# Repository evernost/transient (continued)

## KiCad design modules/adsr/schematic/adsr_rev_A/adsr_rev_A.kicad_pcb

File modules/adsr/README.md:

# ADSR - Contour Generator

Contour Generator: Attack, Decay, Sustain, Release.

---

## Overview

- **Type:** Envelope Generator
- **Domain:** Analog
- **Status:** Work in progress

Block diagram: TODO!

---

## Features
- End of ADSR status (required for the voice assignment in polyphony)

---

## Interfaces

### Inputs
| Name | Type | Range | Description |
|-----|------|-------|-------------|
| IN | Audio | ±1V | Input signal |
| AMP_CV | Analog | 0–5 V | Volume control |

### Outputs
| Name | Type | Description |
|------|------|-------------|
| OUT | Audio | Filtered signal |

---

## Controls

| Control | Type | Description |
|--------|------|-------------|
| Cutoff | Potentiometer | Manual cutoff frequency |
| Resonance | Potentiometer | Feedback amount |

---

## Electrical Characteristics

- **Supply voltage:** +/-12V
- **Current consumption:** TBD mA
- **Signal levels:** TBD

---

## Implementation Notes
Section is TODO.

---

## Files

| File                          | Description                           |
|-------------------------------|---------------------------------------|
| `adsr_rev_A.pdf`              | Electrical schematic (PDF export)     |
| `adsr_rev_A.kicad_sch`        | Schematic (KiCad 10.0.8)              |
| `adsr_rev_A.kicad_pcb`        | PCB layout (KiCad 10.0.8)             |
| `sim/adsr_output_stage.asc`   | SPICE simulation of the output buffer |

---

## Tools
Designed with KiCAD 10.0.8

### KiCAD Grid Settings

| Name   | Size    | Description        |
|--------|---------|--------------------|
| Grid 1 | 0.25 mm | PCB outline        |
| Grid 2 | 25 mil  | Parts placement    |
| Grid 3 | 25 mil  | Routing            |

**Rationale**: Grid 2 and Grid 3 were initially 50 mil, but turned out to be too coarse for precise tracks.

### KiCAD Track settings

| Name    | Size   | Description                |
|---------|--------|----------------------------|
| Class 1 | 500 um | Regular tracks (signal)    |
| Class 2 | 800 um | Power tracks               |

---

## Calibration / Tuning
- Tune the bias voltage on $Q_5$ and $Q_{11}$
- Tune the quiescent current 
- Tune the overload threshold

---

## Known Issues / TODO

- [ ] Make the bias point higher: 1.6V might clip too early
- [ ] Add a reverse polarity protection

---

## Revision History

| Revision  | Date          | Notes             |
|-----------|---------------|-------------------|
| Rev A     | YYYY-MM-DD    | First prototype   |
| Rev B     | YYYY-MM-DD    |                   |

---

## Related Modules

Links to other submodules in the repository:
- `../vca/`
- `../ring_modulator/`

---

## References
- ARP Odyssey Schematic

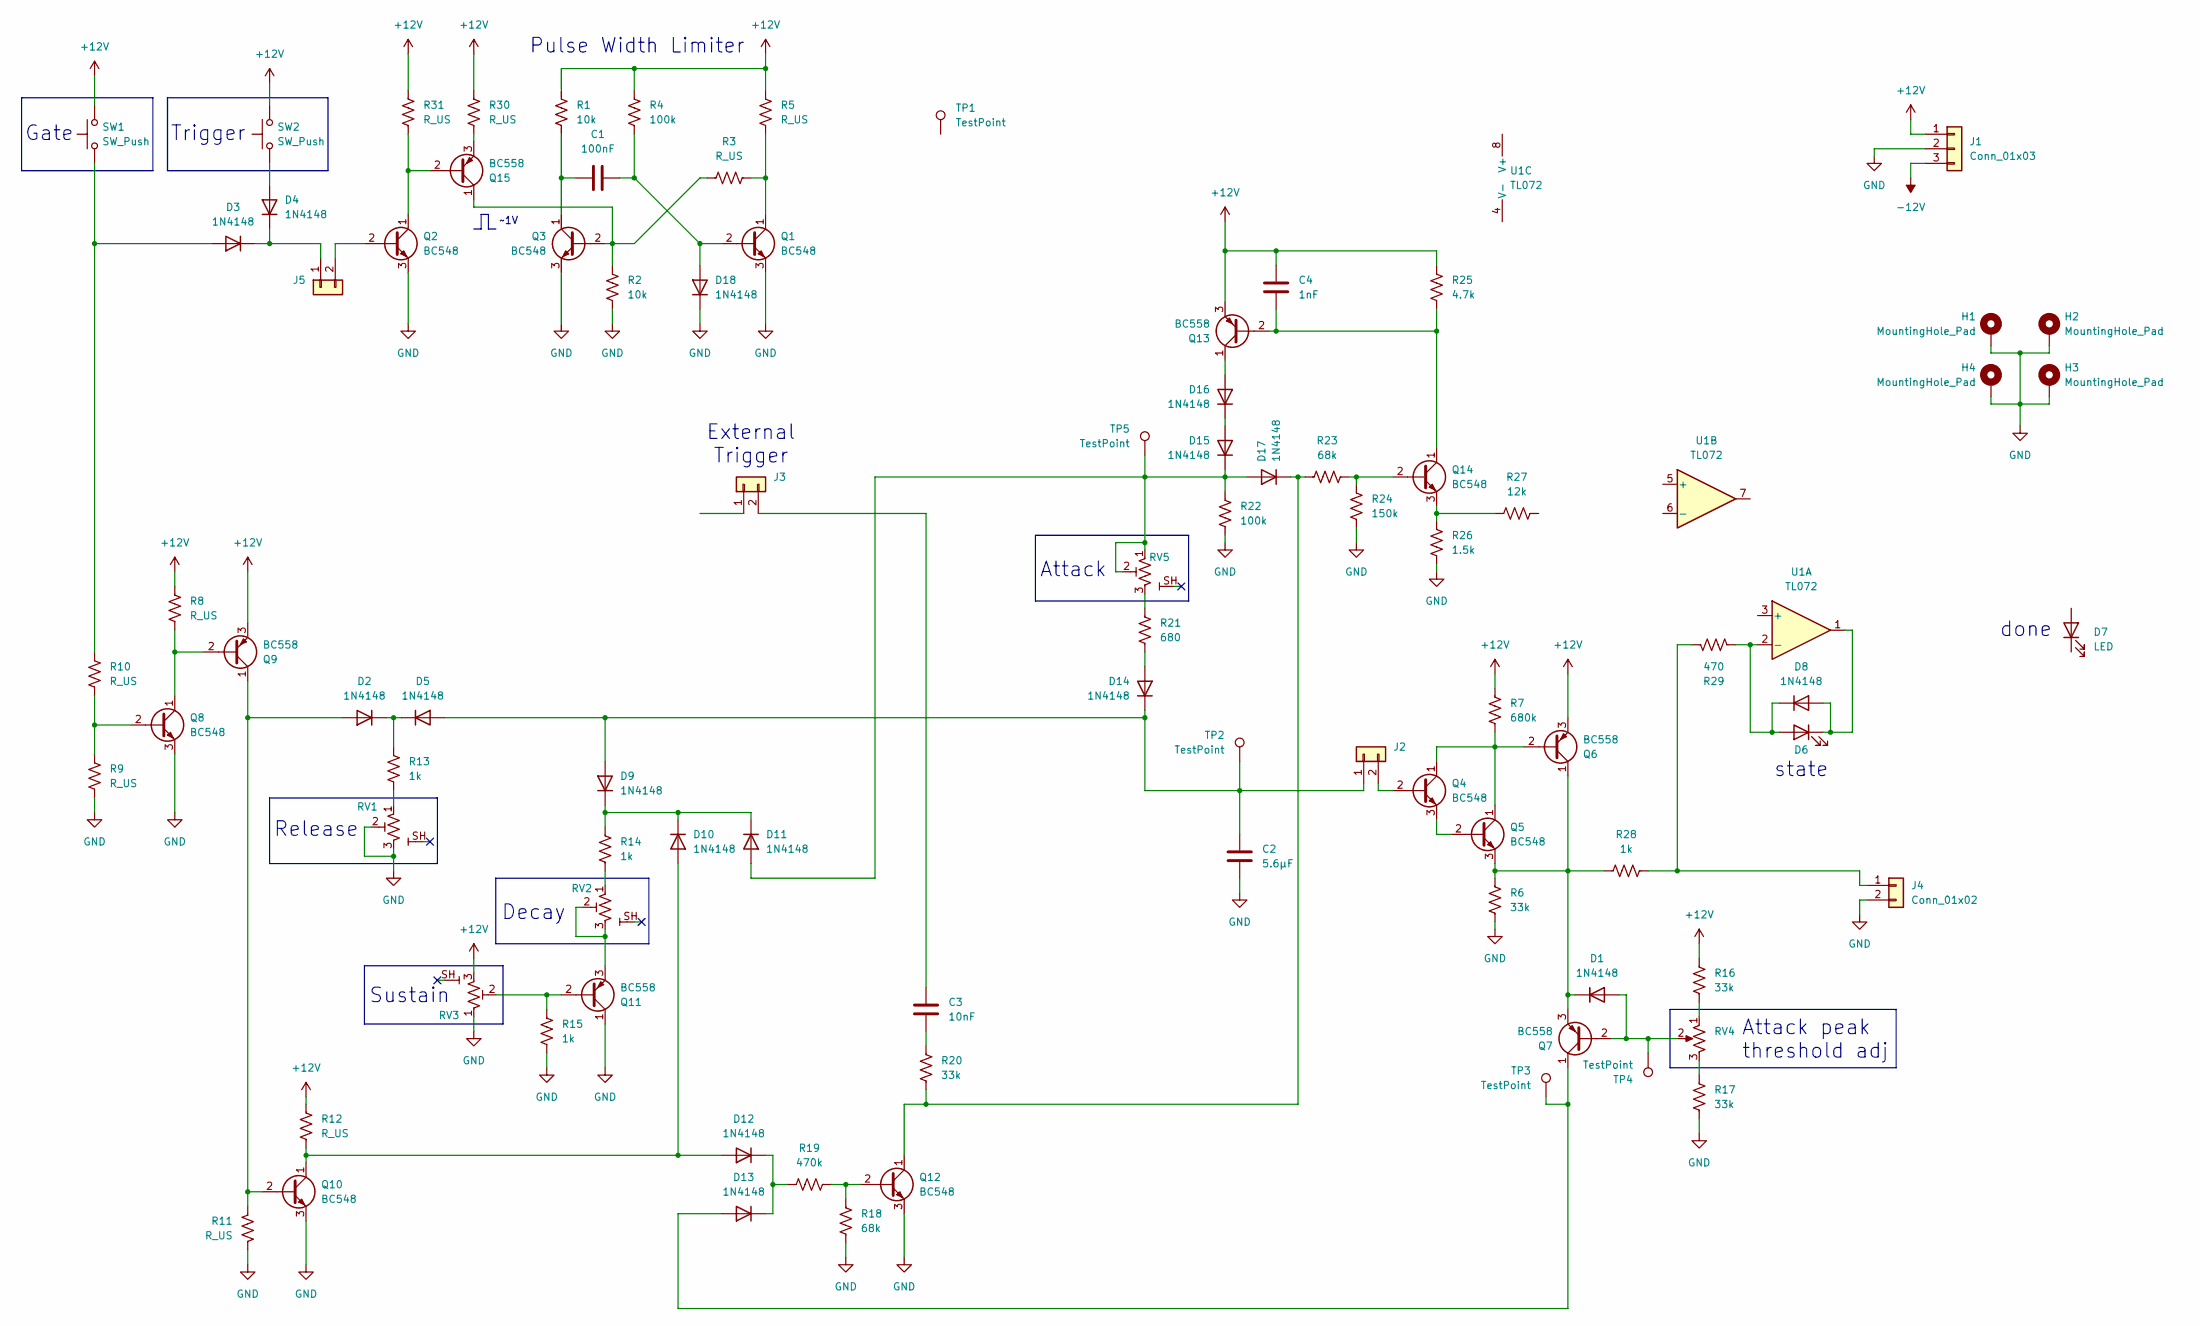
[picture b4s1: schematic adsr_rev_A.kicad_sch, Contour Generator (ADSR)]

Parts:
C1: 100nF; C_Rect_L7.0mm_W2.0mm_P5.00mm
C2: 5.6µF; C_Rect_L13.0mm_W6.0mm_P10.00mm_FKS3_FKP3_MKS4
C3: 10nF; C_Rect_L13.0mm_W6.0mm_P10.00mm_FKS3_FKP3_MKS4
C4: 1nF; C_Rect_L13.0mm_W6.0mm_P10.00mm_FKS3_FKP3_MKS4
D1, D2, D3, D4, D5, D8, D9, D10, D11, D12, D13, D14, D15, D16, D17, D18: 1N4148; D_DO-35_SOD27_P10.16mm_Horizontal
D6, D7: LED; LED_D3.0mm
H1, H2, H3, H4: MountingHole_Pad; MountingHole_3.2mm_M3_Pad_Via
J1: Conn_01x03; WuerthElectronik_WR_TBL_Series_2545_1x03_P5.08mm_Horizontal
J2, J3, J4, J5: Conn_01x02; PinHeader_1x02_P2.54mm_Vertical
Q1, Q2, Q3, Q4, Q5, Q8, Q10, Q12, Q14: BC548; TO-92L_Inline_Wide
Q6, Q7, Q9, Q11, Q13, Q15: BC558; TO-92L_Inline_Wide
R1, R2: 10k; R_Axial_DIN0207_L6.3mm_D2.5mm_P10.16mm_Horizontal
R3, R5, R8, R9, R10, R11, R12, R30, R31: R_US; R_Axial_DIN0207_L6.3mm_D2.5mm_P10.16mm_Horizontal
R4, R22: 100k; R_Axial_DIN0207_L6.3mm_D2.5mm_P10.16mm_Horizontal
R6, R16, R17, R20: 33k; R_Axial_DIN0207_L6.3mm_D2.5mm_P10.16mm_Horizontal
R7: 680k; R_Axial_DIN0207_L6.3mm_D2.5mm_P10.16mm_Horizontal
R13, R14, R15, R28: 1k; R_Axial_DIN0207_L6.3mm_D2.5mm_P10.16mm_Horizontal
R18, R23: 68k; R_Axial_DIN0207_L6.3mm_D2.5mm_P10.16mm_Horizontal
R19: 470k; R_Axial_DIN0207_L6.3mm_D2.5mm_P10.16mm_Horizontal
R21: 680; R_Axial_DIN0207_L6.3mm_D2.5mm_P10.16mm_Horizontal
R24: 150k; R_Axial_DIN0207_L6.3mm_D2.5mm_P10.16mm_Horizontal
R25: 4.7k; R_Axial_DIN0207_L6.3mm_D2.5mm_P10.16mm_Horizontal
R26: 1.5k; R_Axial_DIN0207_L6.3mm_D2.5mm_P10.16mm_Horizontal
R27: 12k; R_Axial_DIN0207_L6.3mm_D2.5mm_P10.16mm_Horizontal
R29: 470; R_Axial_DIN0207_L6.3mm_D2.5mm_P10.16mm_Horizontal
RV1, RV2, RV3, RV5: R_Potentiometer_Shield_US; Potentiometer_Bourns_PTV09A-4_Single_Vertical
RV4: R_Potentiometer_US; Potentiometer_Bourns_3296W_Vertical
SW1, SW2: SW_Push; SW_Push_1P1T_NO_CK_KSC6xxG
TP1, TP2, TP3, TP4, TP5: TestPoint; TestPoint_Pad_D2.0mm
U1: TL072; DIP-8_W7.62mm_LongPads

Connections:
+12V: C4.1, J1.1, Q6.3 (E), Q9.3 (E), Q13.3 (E), R1.1, R4.1, R5.1, R7.1, R8.1, R12.1, R16.1, R25.2, R30.1, R31.1, RV3.3 (B), SW1.2, SW2.2
-12V: J1.3
GND: C2.2, D18.1 (K), H1.1 (1_1), H2.1 (1_1), H3.1 (1_1), H4.1 (1_1), J1.2, J4.2, Q1.3 (E), Q2.3 (E), Q3.3 (E), Q8.3 (E), Q10.3 (E), Q11.1 (C), Q12.3 (E), R2.2, R6.2, R9.2, R11.2, R15.2, R17.2, R18.2, R22.2, R24.1, R26.1, RV1.2 (W), RV1.3 (B), RV3.1 (A)
unnamed: C3.2, R20.1
unnamed: D1.2 (A), Q7.2 (B), RV4.2, TP4.1 (1_1)
unnamed: D1.1 (K), Q5.3 (E), Q6.1 (C), Q7.3 (E), R6.1, R28.2
unnamed: D2.2 (A), Q9.1 (C), Q10.2 (B), R11.1
unnamed: D2.1 (K), D5.1 (K), R13.1
unnamed: D3.2 (A), R10.1, SW1.1
unnamed: D3.1 (K), D4.1 (K), J5.1
unnamed: D4.2 (A), SW2.1
unnamed: D6.2 (A), D8.1 (K), R29.1, U1.2 (-_2)
unnamed: D6.1 (K), D8.2 (A), U1.1
unnamed: D10.2 (A), D12.2 (A), Q10.1 (C), R12.2
unnamed: D9.1 (K), D10.1 (K), D11.1 (K), R14.1
unnamed: D11.2 (A), D15.1 (K), D17.2 (A), R22.1, RV5.1 (A), RV5.2 (W), TP5.1 (1_1)
unnamed: D12.1 (K), D13.1 (K), R19.1
unnamed: D13.2 (A), Q7.1 (C), TP3.1 (1_1)
unnamed: D14.2 (A), R21.2
unnamed: C2.1, D5.2 (A), D9.2 (A), D14.1 (K), J2.1, TP2.1 (1_1)
unnamed: D15.2 (A), D16.1 (K)
unnamed: D16.2 (A), Q13.1 (C)
unnamed: D17.1 (K), Q12.1 (C), R20.2, R23.1
unnamed: C1.2, D18.2 (A), Q1.2 (B), R4.2
unnamed: J2.2, Q4.2 (B)
unnamed: C3.1, J3.2 (Pin_2_2)
unnamed: J4.1, R28.1, R29.2
unnamed: J5.2, Q2.2 (B)
unnamed: Q1.1 (C), R3.2, R5.2
unnamed: C1.1, Q3.1 (C), R1.2
unnamed: Q4.1 (C), Q5.1 (C), Q6.2 (B), R7.2
unnamed: Q4.3 (E), Q5.2 (B)
unnamed: Q8.2 (B), R9.1, R10.2
unnamed: Q8.1 (C), Q9.2 (B), R8.2
unnamed: Q11.2 (B), R15.1, RV3.2 (W)
unnamed: Q11.3 (E), RV2.2 (W), RV2.3 (B)
unnamed: Q12.2 (B), R18.1, R19.2
unnamed: C4.2, Q13.2 (B), Q14.1 (C), R25.1
unnamed: Q14.2 (B), R23.2, R24.2
unnamed: Q14.3 (E), R26.2, R27.2
unnamed: Q2.1 (C), Q15.2 (B), R31.2
unnamed: Q3.2 (B), Q15.1 (C), R2.1, R3.1
unnamed: Q15.3 (E), R30.2
unnamed: R16.2, RV4.1
unnamed: R17.1, RV4.3
unnamed: R13.2, RV1.1 (A)
unnamed: R14.2, RV2.1 (A)
unnamed: R21.1, RV5.3 (B)

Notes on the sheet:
Decay
Attack peak threshold adj
Trigger
Gate
Pulse Width Limiter
External Trigger
Attack
Release
~1V
Sustain
state
done

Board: 2 copper layers, 90 parts (0 on the bottom side), 47 nets, no tracks yet.

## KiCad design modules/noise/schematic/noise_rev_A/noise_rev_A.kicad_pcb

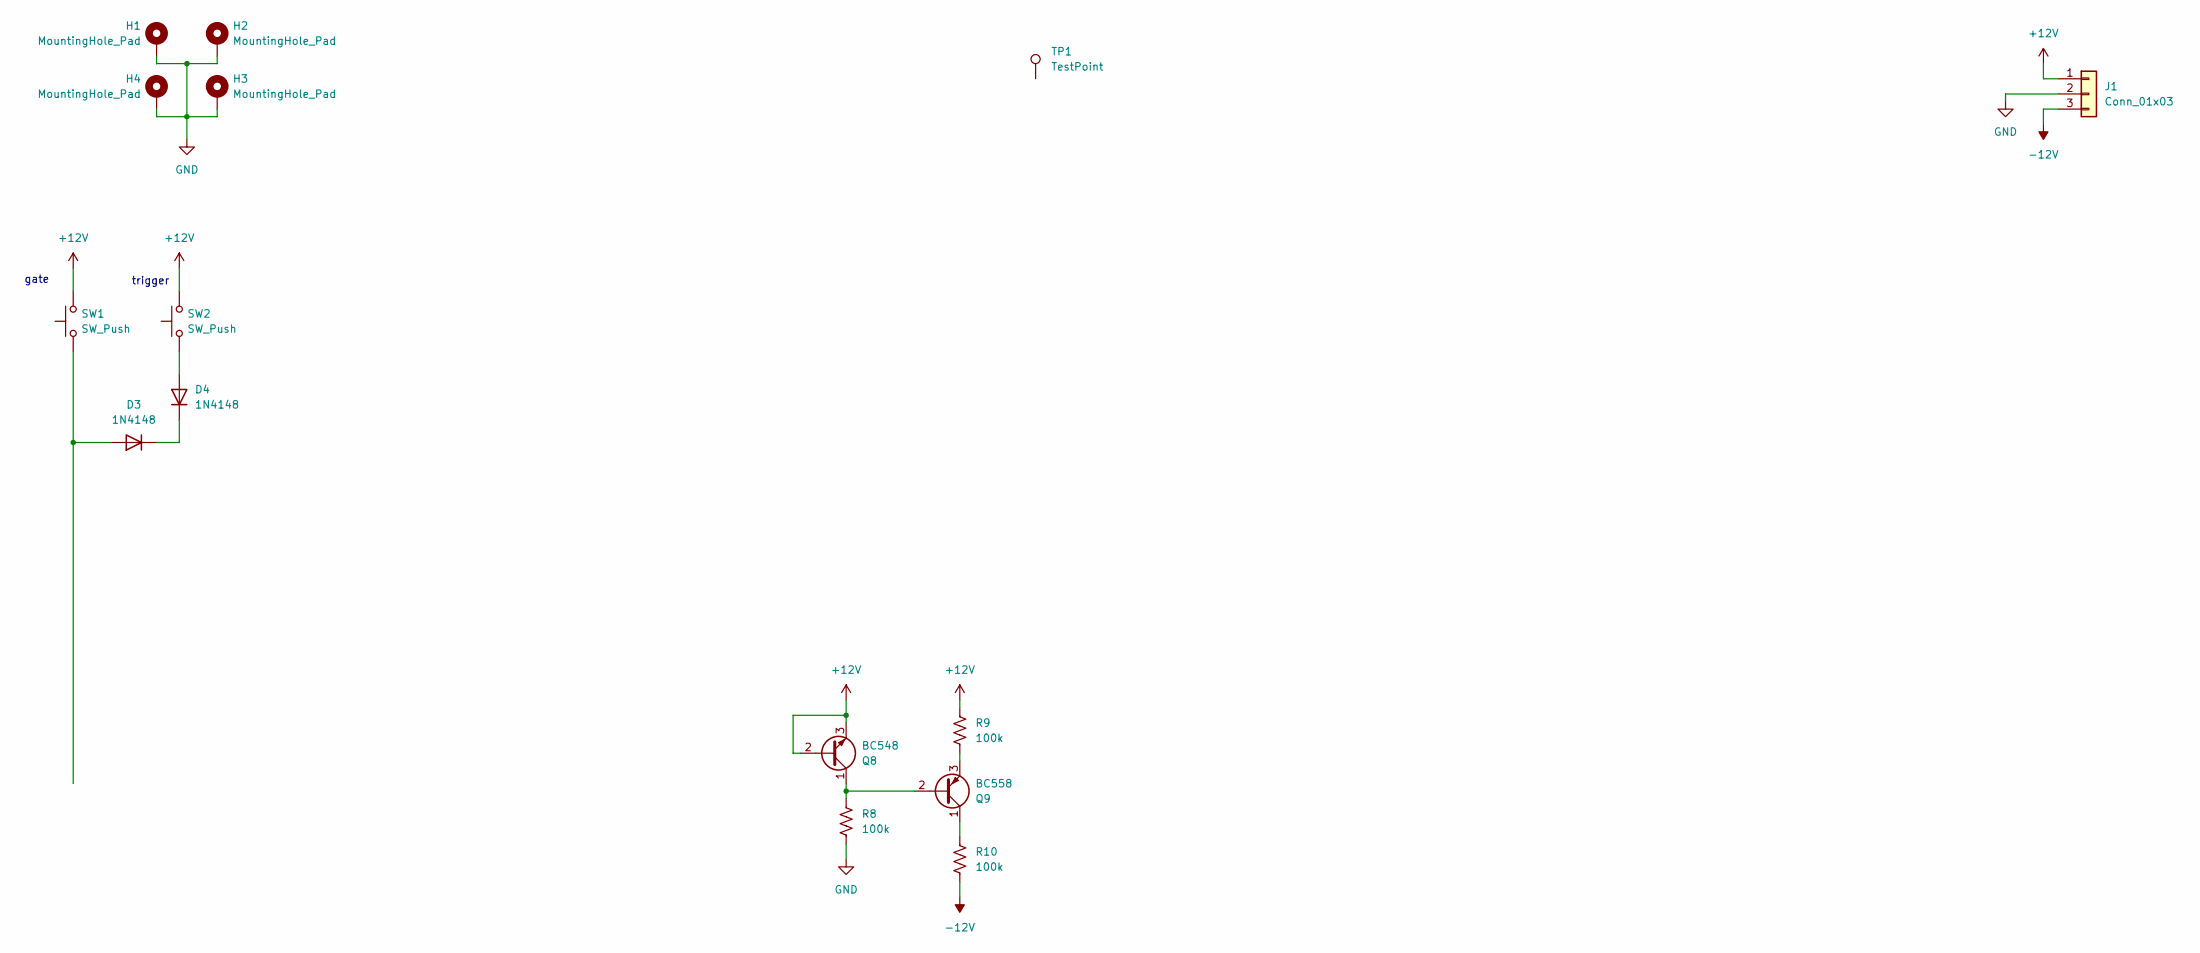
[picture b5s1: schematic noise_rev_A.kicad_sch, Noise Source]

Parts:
D3, D4: 1N4148; D_DO-35_SOD27_P10.16mm_Horizontal
H1, H2, H3, H4: MountingHole_Pad; MountingHole_3.2mm_M3_Pad_Via
J1: Conn_01x03; WuerthElectronik_WR_TBL_Series_2545_1x03_P5.08mm_Horizontal
Q8: BC548; TO-92L_Inline_Wide
Q9: BC558; TO-92L_Inline_Wide
R8, R9, R10: 100k; R_Axial_DIN0207_L6.3mm_D2.5mm_P10.16mm_Horizontal
SW1, SW2: SW_Push; SW_Push_1P1T_NO_CK_KSC6xxG
TP1: TestPoint; TestPoint_Pad_D2.0mm

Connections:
+12V: J1.1, Q8.2 (B), Q8.3 (E), R9.1, SW1.2, SW2.2
-12V: J1.3, R10.2
GND: H1.1 (1_1), H2.1 (1_1), H3.1 (1_1), H4.1 (1_1), J1.2, R8.2
unnamed: D3.2 (A), SW1.1
unnamed: D3.1 (K), D4.1 (K)
unnamed: D4.2 (A), SW2.1
unnamed: Q8.1 (C), Q9.2 (B), R8.1
unnamed: Q9.1 (C), R10.1
unnamed: Q9.3 (E), R9.2

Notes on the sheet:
trigger
gate

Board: 2 copper layers, 15 parts (0 on the bottom side), 9 nets, no tracks yet.

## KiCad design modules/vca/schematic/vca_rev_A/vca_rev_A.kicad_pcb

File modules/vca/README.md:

# VCA Module

A simple analog Voltage-Controlled Amplifier for audio signals.

---

## Overview

- **Type:** VCA
- **Domain:** Analog
- **Status:** Work in progress

Block diagram: TODO!

---

## Features
- **Overdrive**: the input can be overdriven on purpose to add _colors_ to the function
- **Control**: linear and logarithmic control

---

## Interfaces

### Inputs
| Name | Type | Range | Description |
|-----|------|-------|-------------|
| IN | Audio | ±1V | Input signal |
| AMP_CV | Analog | 0–5 V | Volume control |

### Outputs
| Name | Type | Description |
|------|------|-------------|
| OUT | Audio | Filtered signal |

---

## Controls

| Control | Type | Description |
|--------|------|-------------|
| Cutoff | Potentiometer | Manual cutoff frequency |

---

## Electrical Characteristics

- **Supply voltage:** ±12V
- **Current consumption:** TBD mA
- **Signal levels:** TBD

---

## Implementation Notes
Section is TODO.

---

## Files

| File                  | Description                       |
|-----------------------|-----------------------------------|
| `vca_rev_A.pdf`       | Electrical schematic (PDF export) |
| `vca_rev_A.kicad_sch` | Schematic (KiCad 10.0.8)          |
| `vca_rev_A.kicad_pcb` | PCB layout (KiCad 10.0.8)         |
| `sim/XXX.asc`         | SPICE simulation                  |

---

## Tools
Designed with KiCAD 10.0.8

### KiCAD Grid Settings

| Name   | Size    | Description        |
|--------|---------|--------------------|
| Grid 1 | 0.25 mm | PCB outline        |
| Grid 2 | 25 mil  | Parts placement    |
| Grid 3 | 25 mil  | Routing            |

**Rationale**: Grid 2 and Grid 3 were initially 50 mil, but turned out to be too coarse for precise tracks.

### KiCAD Track settings

| Name    | Size   | Description                |
|---------|--------|----------------------------|
| Class 1 | 500 um | Regular traces (signal)    |
| Class 2 | 800 um | Power traces               |

---

## Calibration / Tuning
No calibration required.

---

## Known Issues / TODO

- [ ] TODO

---

## Revision History

| Revision | Date | Notes |
|--------|------|-------|
| Rev A | YYYY-MM-DD | Initial prototype |

---

## Related Modules

Links to other submodules in the repository:
- `../vca/`
- `../ring_modulator/`

---

## References

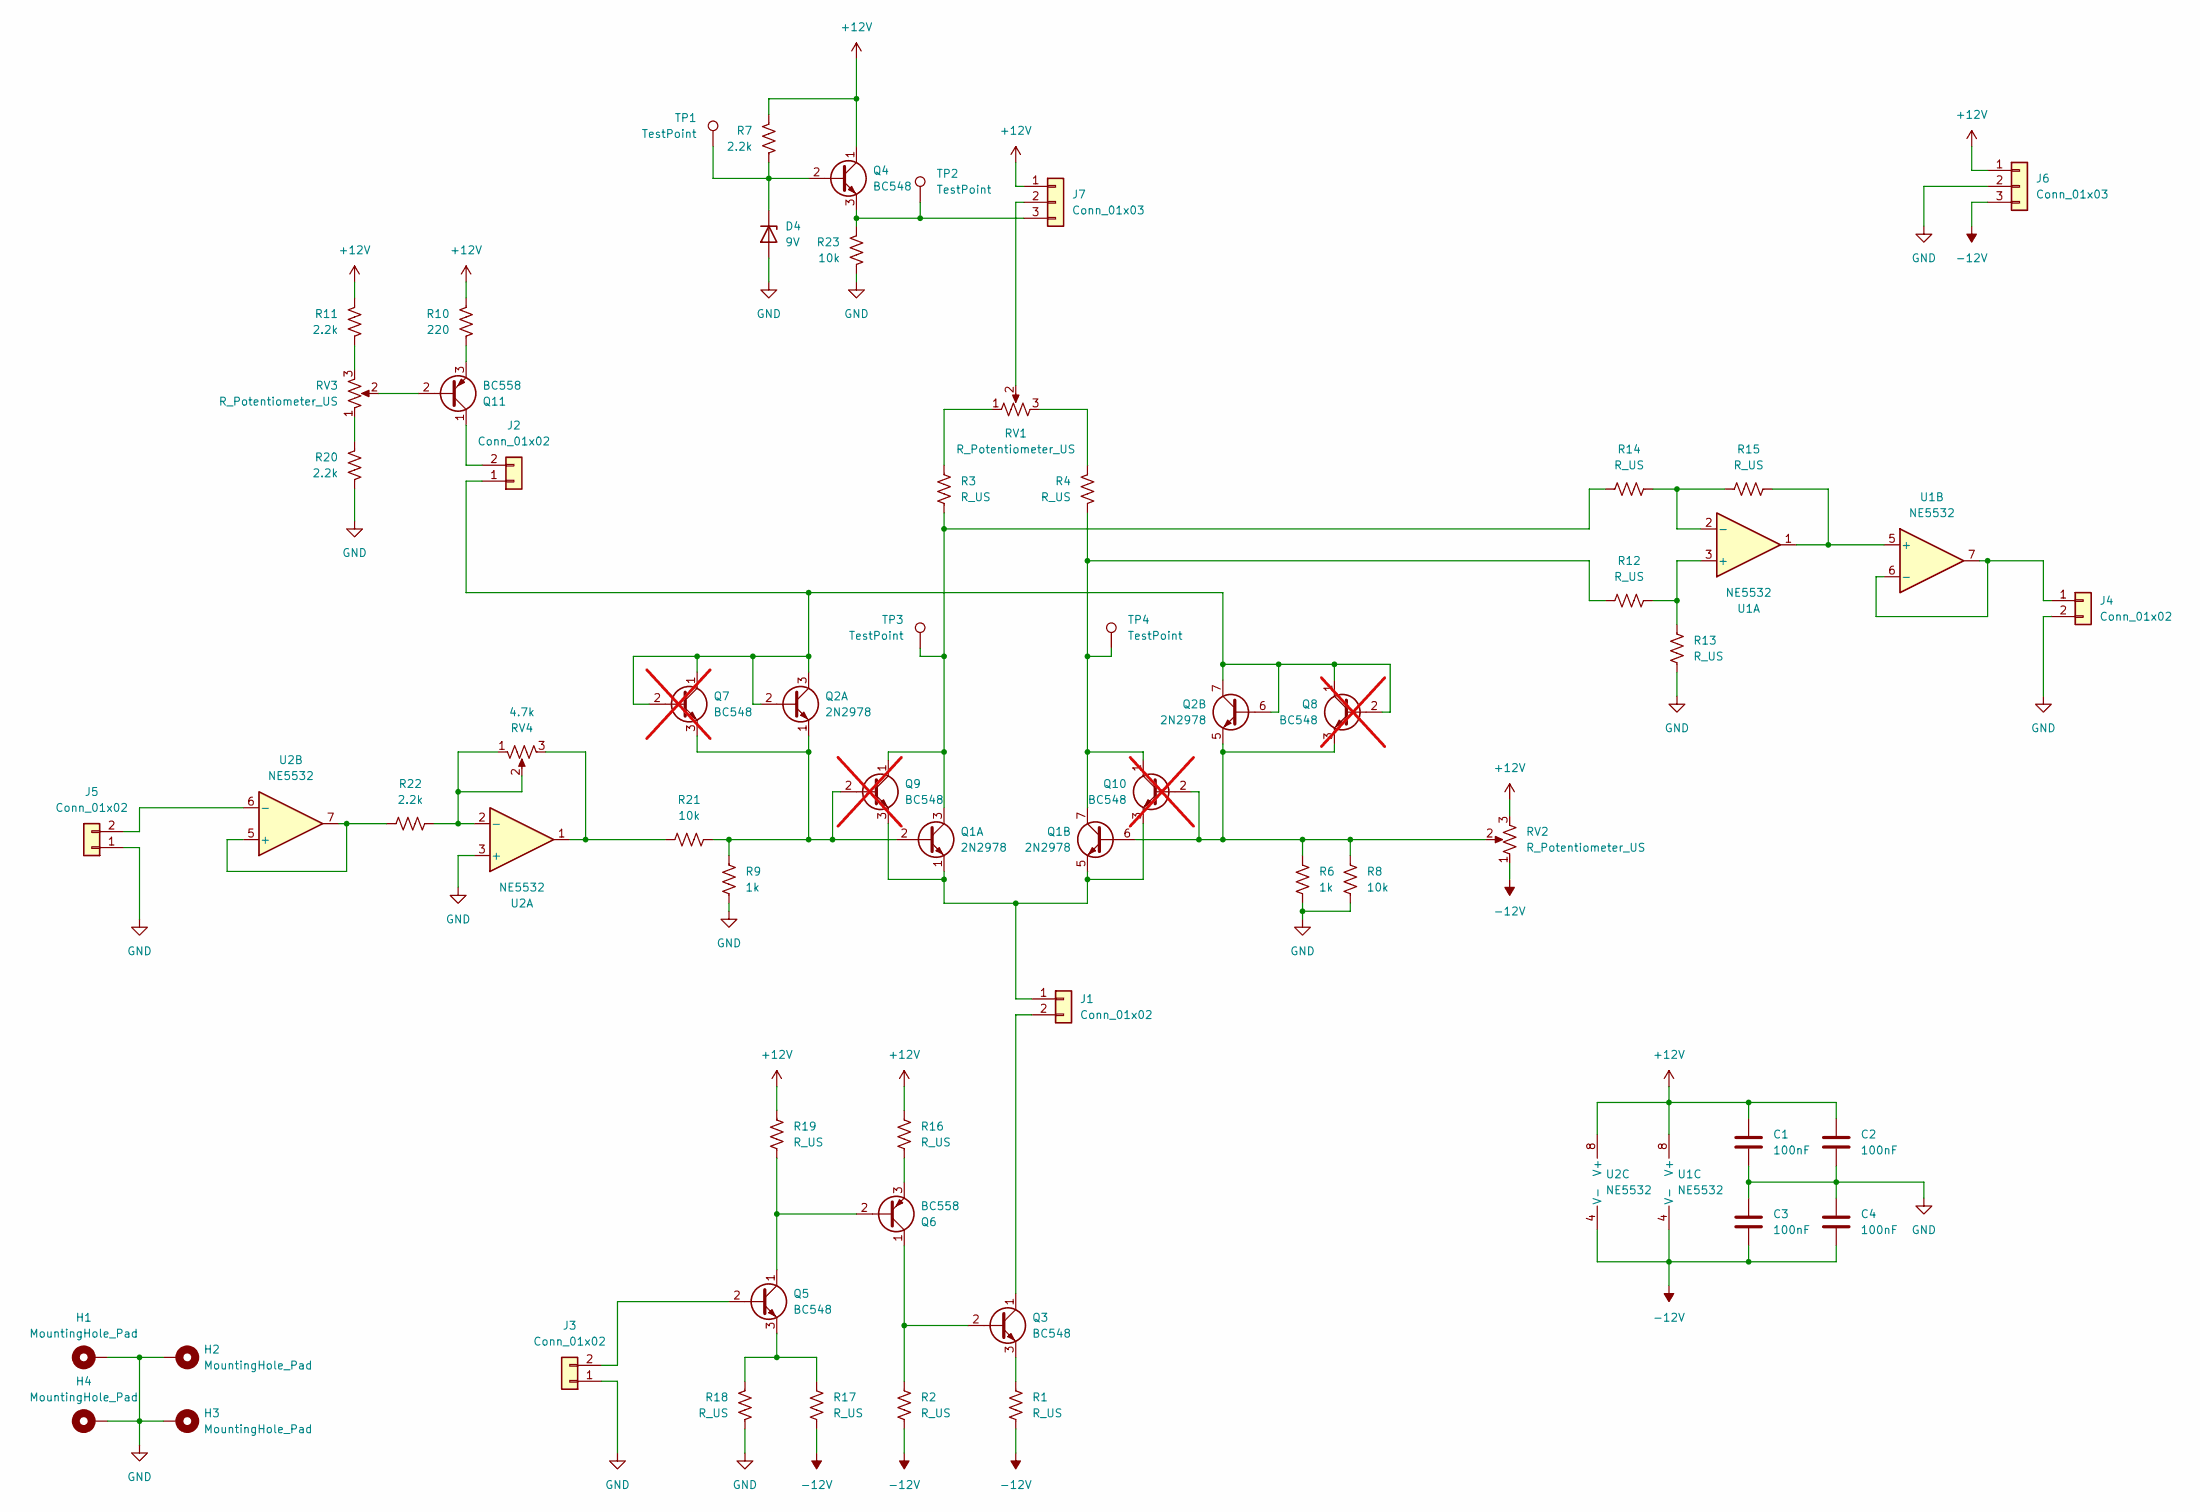
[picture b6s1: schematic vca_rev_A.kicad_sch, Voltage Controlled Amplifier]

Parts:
C1, C2, C3, C4: 100nF; C_Rect_L7.0mm_W2.0mm_P5.00mm
D4: 9V; D_DO-41_SOD81_P10.16mm_Horizontal
H1, H2, H3, H4: MountingHole_Pad; MountingHole_3.2mm_M3_Pad_Via
J1, J2, J3, J4, J5: Conn_01x02; PinHeader_1x02_P2.54mm_Vertical
J6: Conn_01x03; WuerthElectronik_WR_TBL_Series_2545_1x03_P5.08mm_Horizontal
J7: Conn_01x03; PinSocket_1x03_P2.54mm_Vertical
Q1, Q2: 2N2978; TO-5-6
Q3, Q4, Q5: BC548; TO-92L_Inline_Wide
Q6, Q11: BC558; TO-92L_Inline_Wide
Q7, Q8, Q9, Q10: BC548; TO-92L_Inline_Wide; not fitted
R1, R2, R3, R4, R12, R13, R14, R15, R16, R17, R18, R19: R_US; R_Axial_DIN0207_L6.3mm_D2.5mm_P10.16mm_Horizontal
R6, R9: 1k; R_Axial_DIN0207_L6.3mm_D2.5mm_P10.16mm_Horizontal
R7, R11, R20, R22: 2.2k; R_Axial_DIN0207_L6.3mm_D2.5mm_P10.16mm_Horizontal
R8, R21, R23: 10k; R_Axial_DIN0207_L6.3mm_D2.5mm_P10.16mm_Horizontal
R10: 220; R_Axial_DIN0207_L6.3mm_D2.5mm_P10.16mm_Horizontal
RV1, RV2, RV3: R_Potentiometer_US; Potentiometer_Bourns_3296W_Vertical
RV4: 4.7k; Potentiometer_Bourns_3296W_Vertical
TP1, TP2, TP3, TP4: TestPoint; TestPoint_Pad_D2.0mm
U1, U2: NE5532; SOIC-8_5.3x6.2mm_P1.27mm

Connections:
+12V: C1.1, C2.1, J6.1, J7.1, Q4.1 (C), R7.1, R10.1, R11.1, R16.1, R19.1, RV2.3, U1.8 (V+), U2.8 (V+)
-12V: C3.2, C4.2, J6.3, R1.2, R2.2, R17.2, RV2.1, U1.4 (V-), U2.4 (V-)
GND: C1.2, C2.2, C3.1, C4.1, D4.2 (A), H1.1 (1_1), H2.1 (1_1), H3.1 (1_1), H4.1 (1_1), J3.1, J4.2, J5.1, J6.2, R6.2, R8.2, R9.2, R13.2, R18.2, R20.2, R23.2, U2.3 (+)
unnamed: D4.1 (K), Q4.2 (B), R7.2, TP1.1 (1_1)
unnamed: J1.1, Q1.1 (E1), Q1.5 (E2), Q9.3 (E), Q10.3 (E)
unnamed: J1.2, Q3.1 (C)
unnamed: J2.1, Q2.2 (B1), Q2.3 (C1), Q2.6 (B2), Q2.7 (C2), Q7.1 (C), Q7.2 (B), Q8.1 (C), Q8.2 (B)
unnamed: J2.2, Q11.1 (C)
unnamed: J3.2, Q5.2 (B)
unnamed: J4.1, U1.6 (-), U1.7
unnamed: J5.2, U2.6 (-)
unnamed: J7.2, RV1.2
unnamed: J7.3, Q4.3 (E), R23.1, TP2.1 (1_1)
unnamed: Q1.2 (B1), Q2.1 (E1), Q7.3 (E), Q9.2 (B), R9.1, R21.2
unnamed: Q1.3 (C1), Q9.1 (C), R3.2, R14.1, TP3.1 (1_1)
unnamed: Q3.2 (B), Q6.1 (C), R2.1
unnamed: Q3.3 (E), R1.1
unnamed: Q5.1 (C), Q6.2 (B), R19.2
unnamed: Q5.3 (E), R17.1, R18.1
unnamed: Q6.3 (E), R16.2
unnamed: Q1.6 (B2), Q2.5 (E2), Q8.3 (E), Q10.2 (B), R6.1, R8.1, RV2.2
unnamed: Q1.7 (C2), Q10.1 (C), R4.2, R12.1, TP4.1 (1_1)
unnamed: Q11.2 (B), RV3.2
unnamed: Q11.3 (E), R10.2
unnamed: R3.1, RV1.1
unnamed: R4.1, RV1.3
unnamed: R11.2, RV3.3
unnamed: R20.1, RV3.1
unnamed: R21.1, RV4.3, U2.1
unnamed: R12.2, R13.1, U1.3 (+)
unnamed: R14.2, R15.1, U1.2 (-)
unnamed: R15.2, U1.1, U1.5 (+)
unnamed: R22.2, RV4.1, RV4.2, U2.2 (-)
unnamed: R22.1, U2.5 (+), U2.7

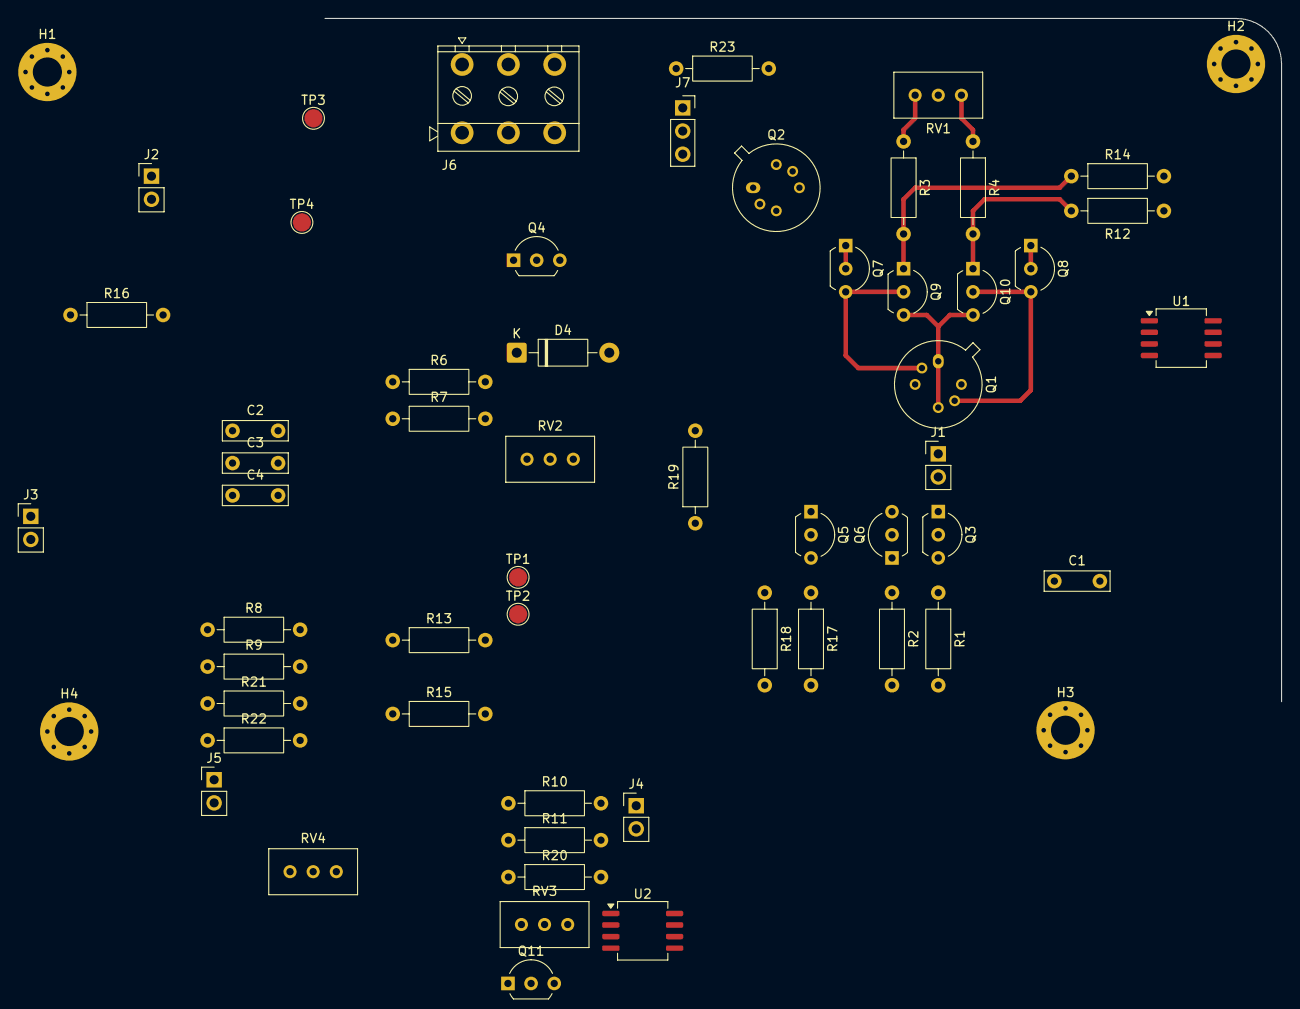
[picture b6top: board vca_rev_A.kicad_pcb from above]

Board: 2 copper layers, 59 parts (0 on the bottom side), 34 nets.

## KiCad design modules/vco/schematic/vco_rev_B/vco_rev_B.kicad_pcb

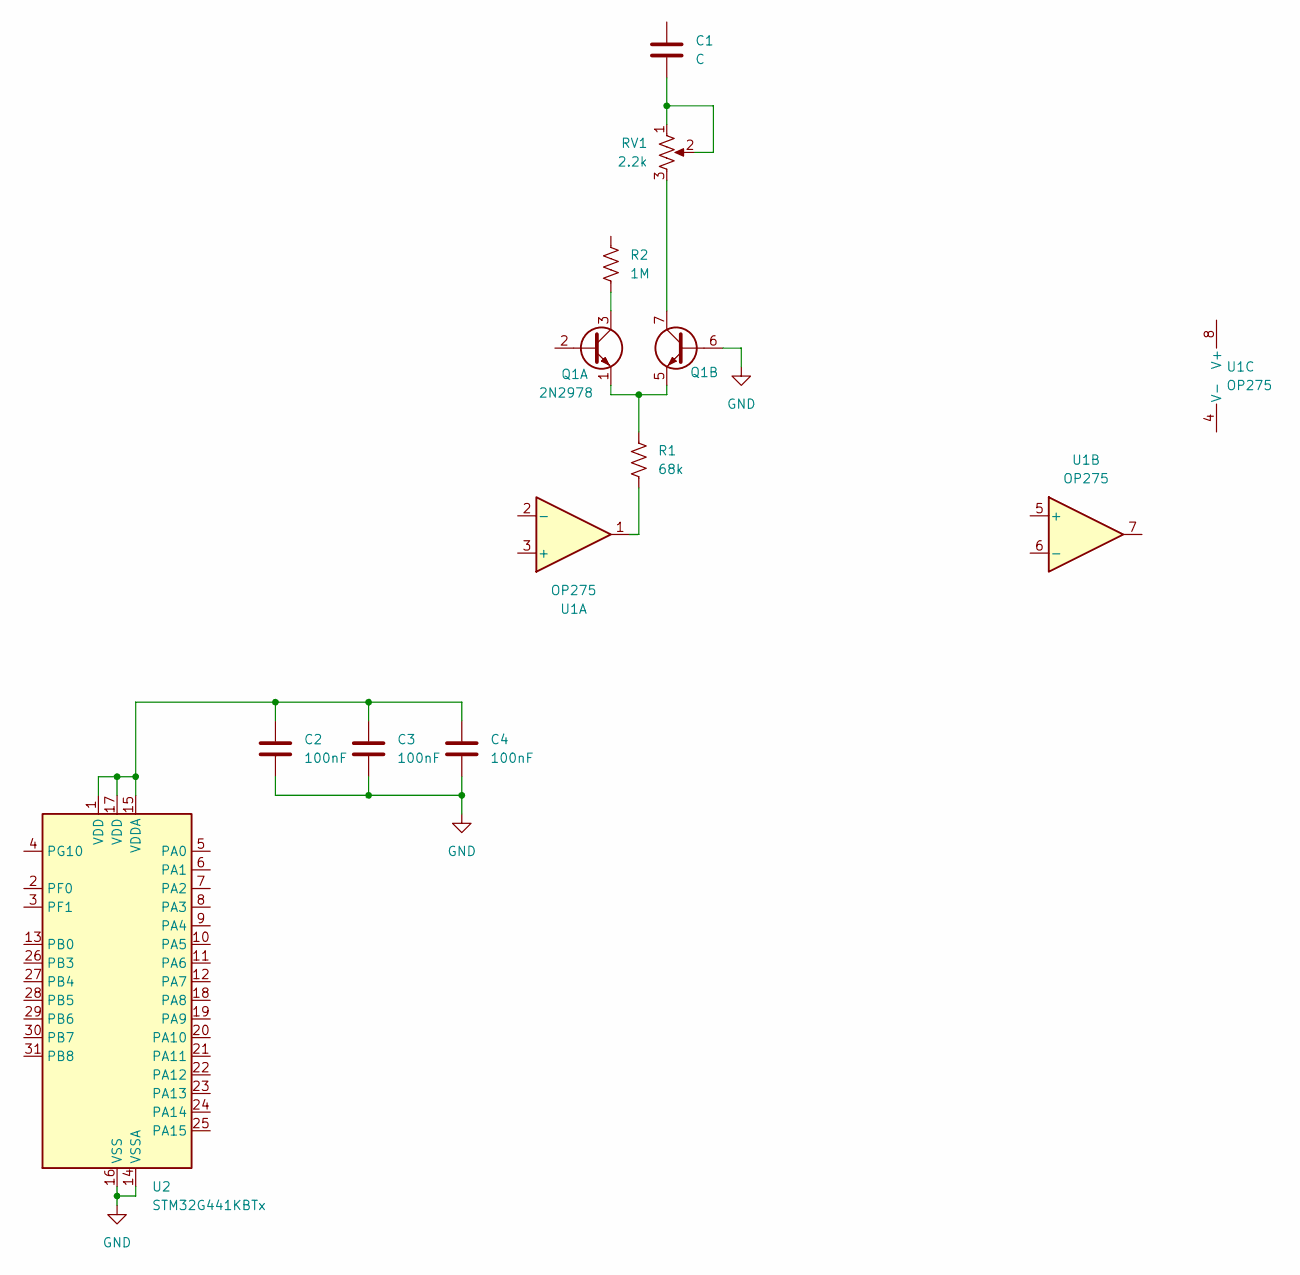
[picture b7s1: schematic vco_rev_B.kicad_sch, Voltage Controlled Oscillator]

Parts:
C1: C; C_Rect_L7.0mm_W2.0mm_P5.00mm
C2, C3, C4: 100nF; C_0805_2012Metric_Pad1.18x1.45mm_HandSolder
Q1: 2N2978; TO-5-6
R1: 68k; R_Axial_DIN0207_L6.3mm_D2.5mm_P10.16mm_Horizontal
R2: 1M; R_Axial_DIN0207_L6.3mm_D2.5mm_P10.16mm_Horizontal
RV1: 2.2k; Potentiometer_Bourns_3296W_Vertical
U1: OP275; DIP-8_W7.62mm_Socket_LongPads
U2: STM32G441KBTx; LQFP-32_7x7mm_P0.8mm

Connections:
GND: C2.2, C3.2, C4.2, Q1.6 (B2), U2.14 (VSSA), U2.16 (VSS), U2.32 (VSS)
unnamed: C1.2, RV1.1, RV1.2
unnamed: Q1.3 (C1), R2.2
unnamed: Q1.1 (E1), Q1.5 (E2), R1.1
unnamed: Q1.7 (C2), RV1.3
unnamed: R1.2, U1.1
unnamed: C2.1, C3.1, C4.1, U2.1 (VDD), U2.15 (VDDA), U2.17 (VDD)

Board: 2 copper layers, 10 parts (0 on the bottom side), 7 nets, no tracks yet.

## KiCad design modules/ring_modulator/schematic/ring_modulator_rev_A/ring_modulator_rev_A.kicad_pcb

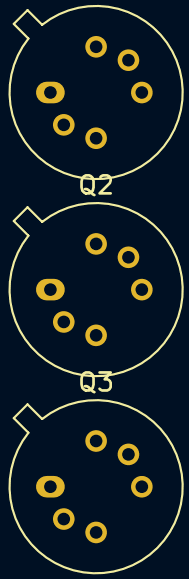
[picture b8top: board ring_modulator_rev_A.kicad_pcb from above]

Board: 2 copper layers, 3 parts (0 on the bottom side), 5 nets, no tracks yet.

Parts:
Q1, Q2, Q3: 2N2978; TO-5-6

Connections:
unnamed: Q1.2 (B1), Q2.6 (B2)
unnamed: Q1.1 (E1), Q1.5 (E2), Q3.3 (C1)
unnamed: Q1.6 (B2), Q2.2 (B1)
unnamed: Q2.1 (E1), Q2.5 (E2), Q3.7 (C2)
unnamed: Q3.1 (E1), Q3.5 (E2)

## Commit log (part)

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2025-10-30 added db for the headphones amplifier
2025-10-31 added the VCA module
2025-11-03 added an overload detector to the headphone amp
2026-01-01 added the VCF submodules added the voltage controlled current sink
2026-01-04 Added project library Added 2N2978
2026-01-13 added the article were justifications will be detailed added framework where the distorsion will be evaluated
2026-01-14 fixed the VCA for the filter in simulation, added sections in the doc for the VCF
2026-01-15 added some more tools, standardised code format
2026-01-18 added schematic for the headphones amplifier
2026-01-19 added reference schematic added dev directories
2026-01-20 updated the schematic for the ring mod to a working example
2026-01-21 added schematic (principle) for the 'rabotnik' module
2026-01-24 added the noise generator module
2026-01-25 updated schematic for the headphones amp and VCF
2026-01-25 renamed the noise module to something more accurate'
2026-01-27 added readme for the VCO
2026-01-27 added the VCA kicad project
2026-01-28 updated descriptions
2026-01-29 added schematic for the noise generator
2026-01-30 added .gitignore definitions added schematics for the ring modulator and vco
2026-01-30 renamed the headphones amplifier project added a list of commonly used parts
2026-01-31 added some docs
2026-02-01 renamed the VCF project files
2026-02-01 added the PPL
2026-02-02 added reference schematics
2026-02-02 added new references to the PPL
2026-02-03 updated the calculations/simulations/schematic for the headphones amp
2026-02-03 restructured the libraries folders
2026-02-04 fixed the path to libraries (relative instead of absolute)
2026-02-05 added first footprint attempt completed the .gitignore list
2026-02-06 added a description for the project library completed the footprint for PTV potentiometer
2026-02-07 added proper silkscreen on PTV potentiometer
2026-02-07 replaced footprint for the PTV potentiometer with an existing version (with minor tweaks)
2026-02-07 updated the Bourns PTV112 updated schematic renamed and upgraded the list of commonly used kicad parts
2026-02-08 added the datasheet of the parts in the PPL
2026-02-08 added footprint for the ANT switch
2026-02-09 updated ignore list updated library with a new switch (ANT)
2026-02-10 added draft footprint for the Wurth Connector
2026-02-11 attempt to fix wrong footprint
2026-02-12 fixed the footprint issue with the PTV
2026-02-13 added datasheets
2026-02-14 added footprint for the 5.08mm board connector
2026-02-15 added outline for the PCB
2026-02-16 updated the pcb outline
2026-02-18 extended PCB outline
2026-02-19 adjusted bias point of the input stage first preplacement of the parts on the board
2026-02-20 fixed the lib path in the VCO project
2026-02-24 updated the article
2026-02-25 updated rubber diode section
2026-03-03 - added a bootstrap structure for improved input impedance - moved the mono/stereo junction point
2026-03-07 input stage: improved biasing (more stable version), added component values (validated on prototype) PCB cleanup (useless footprints)
2026-03-09 added project for the Phasing module
2026-03-10 first routing of the PCB added a case study for the phaser
2026-03-11 added an article about the phaser derivation + illustrating simulation
2026-03-12 updated pcb layout
2026-03-16 added on board measurements
2026-03-18 progress backup
2026-03-19 PCB progress backup
2026-03-22 PCB progress backup All parts finally fit in the board!
2026-03-23 added a PDF export of the schematic
2026-03-24 added STM32 preliminary project for the VCO
2026-06-06 progressed on the routing
